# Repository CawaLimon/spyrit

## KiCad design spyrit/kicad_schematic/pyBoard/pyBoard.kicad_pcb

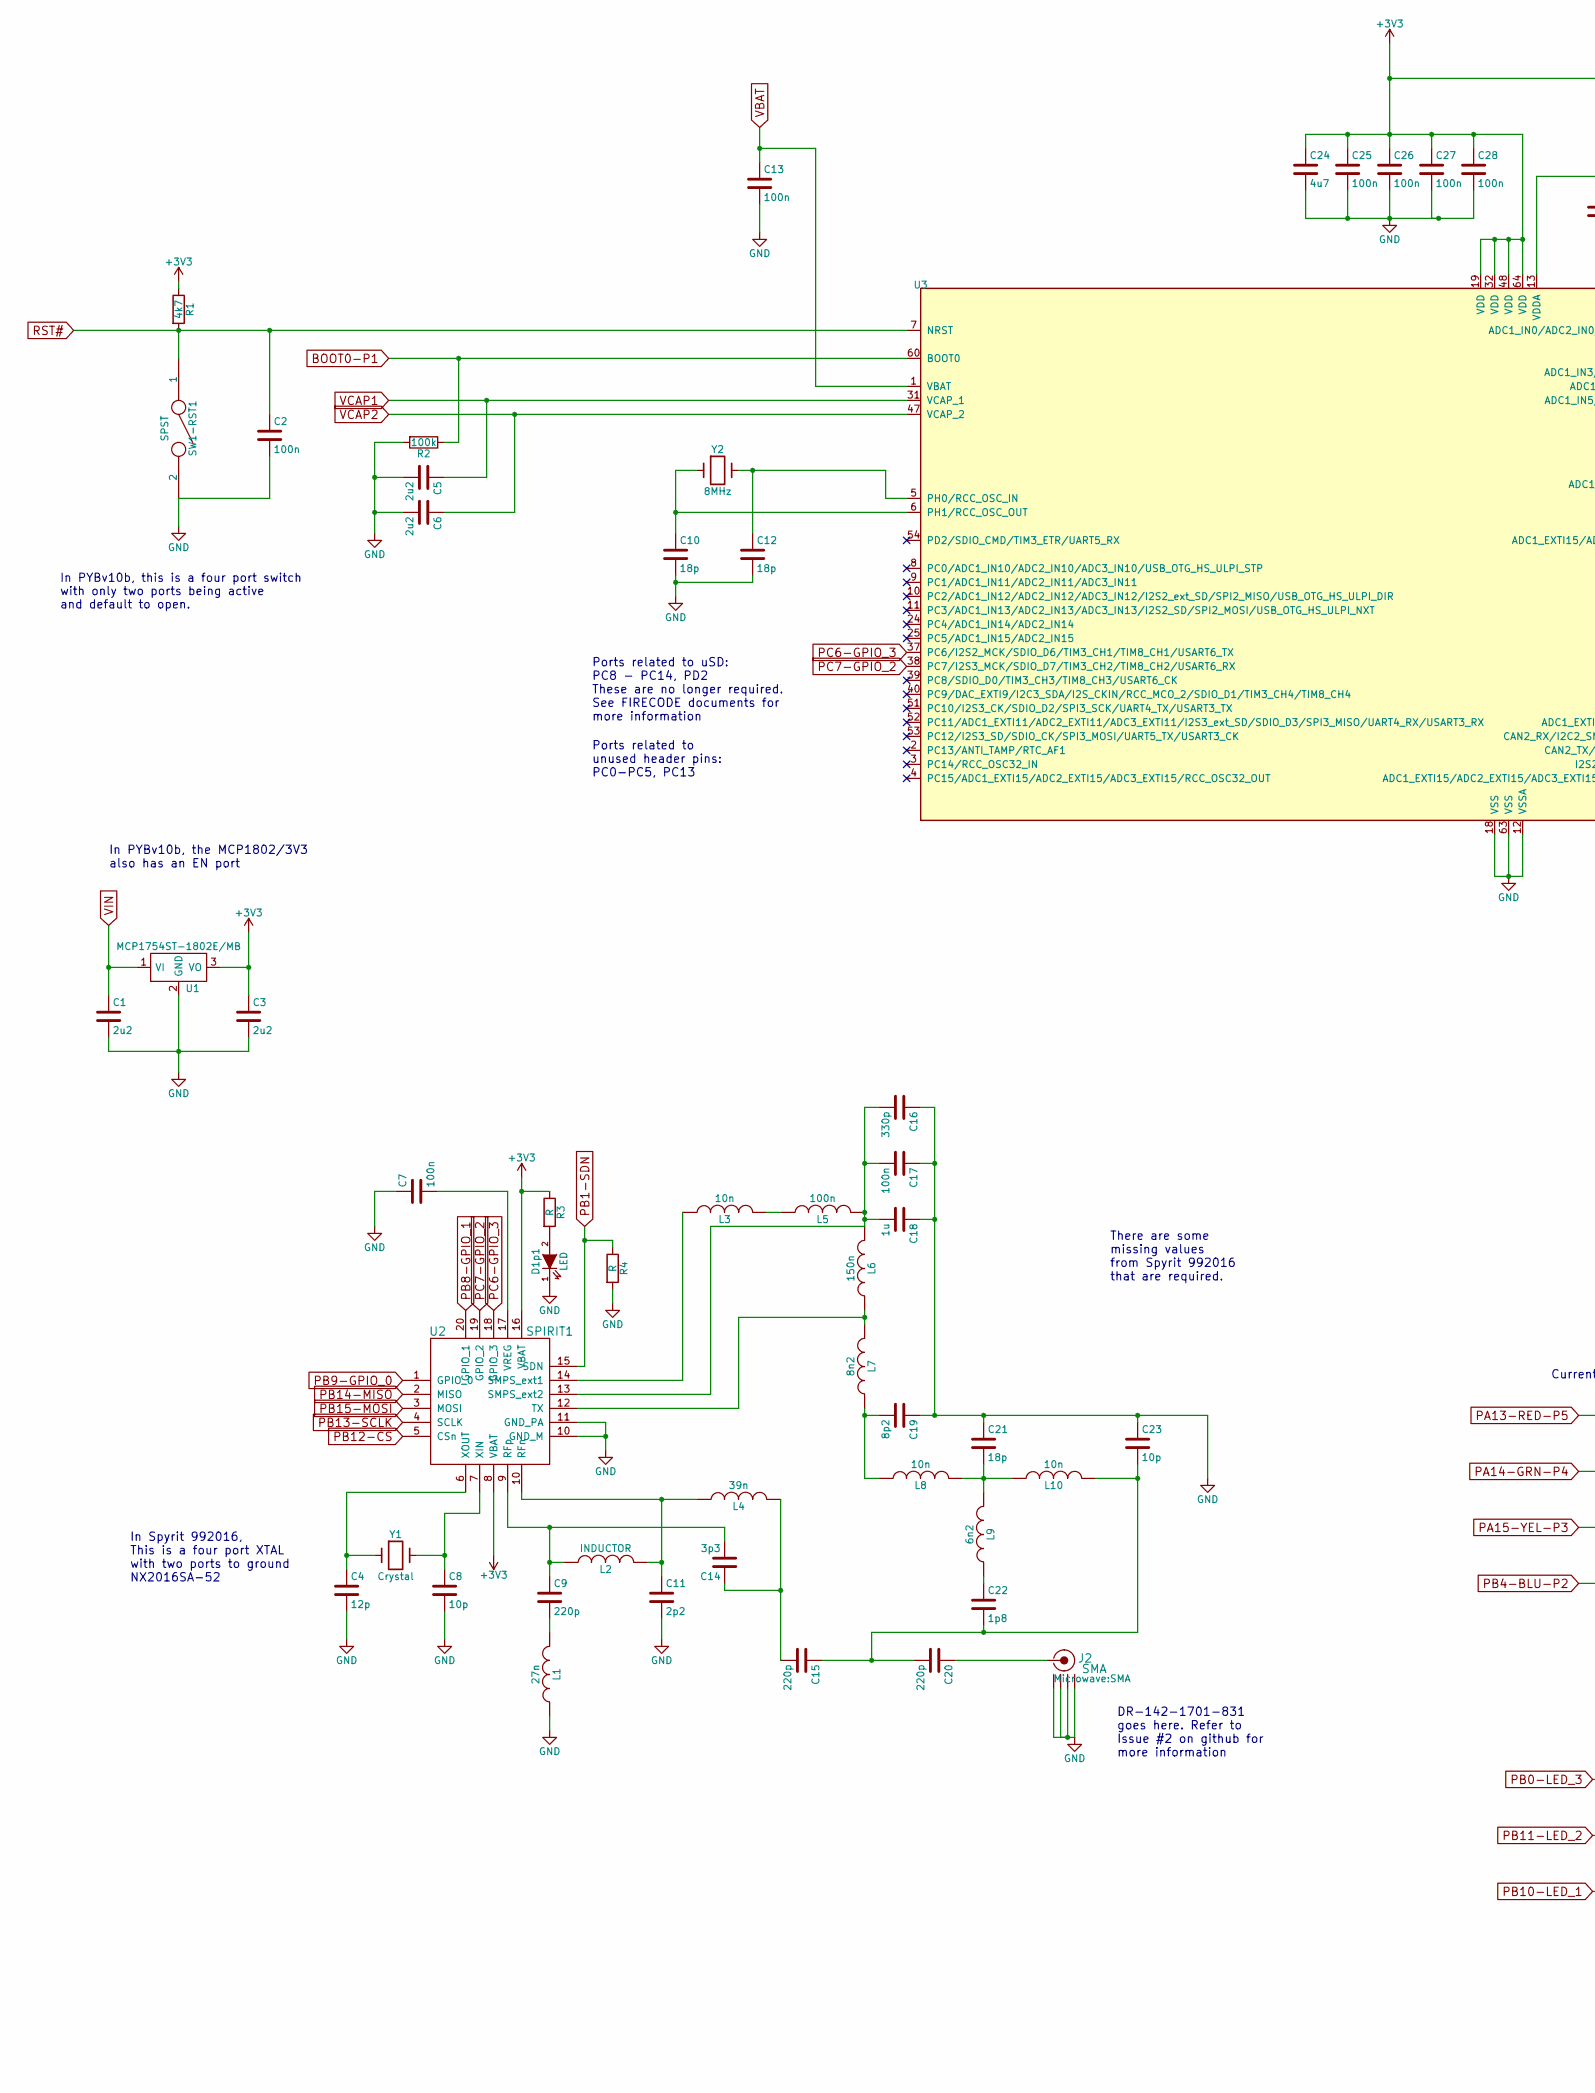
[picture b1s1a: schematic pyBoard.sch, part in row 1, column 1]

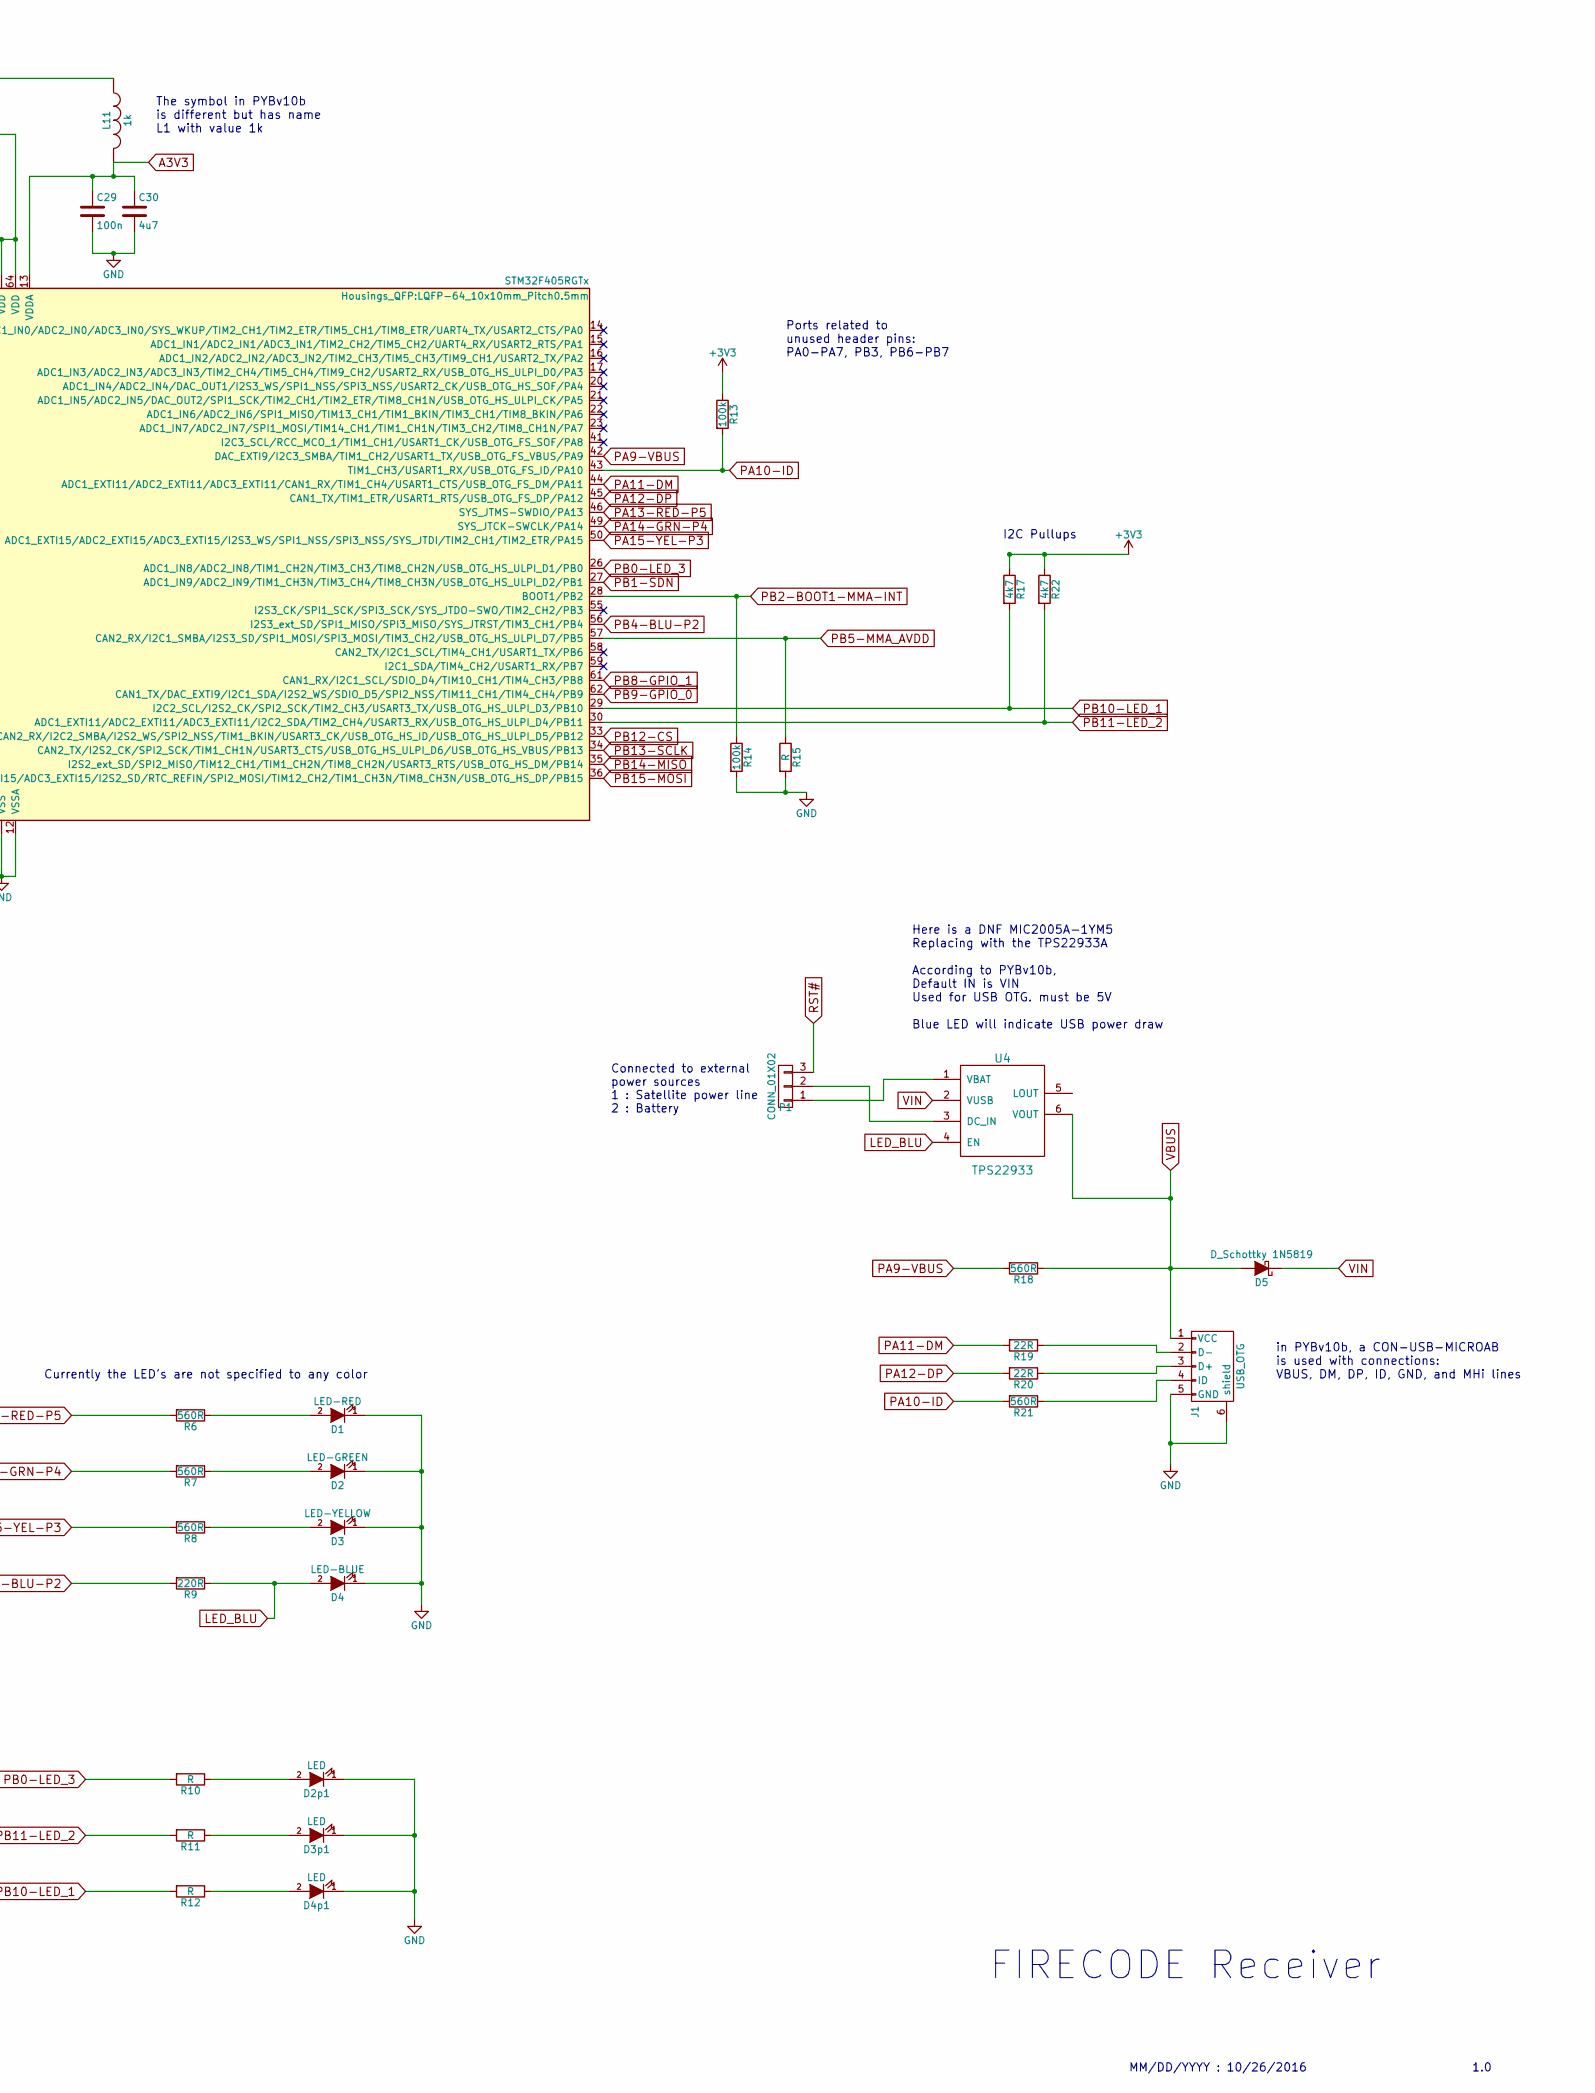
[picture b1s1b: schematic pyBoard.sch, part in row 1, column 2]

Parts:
C1, C3, C5, C6: 2u2; C_0603_HandSoldering
C2, C7, C13, C17, C25, C26, C27, C28, C29: 100n; C_0603_HandSoldering
C4: 12p; C_0603_HandSoldering
C8, C23: 10p; C_0603_HandSoldering
C9, C15, C20: 220p; C_0603_HandSoldering
C10, C12, C21: 18p; C_0603_HandSoldering
C11: 2p2; C_0603_HandSoldering
C14: 3p3; C_0603_HandSoldering
C16: 330p; C_0603_HandSoldering
C18: 1u; C_0603_HandSoldering
C19: 8p2; C_0603_HandSoldering
C22: 1p8; C_0603_HandSoldering
C24, C30: 4u7; C_0603_HandSoldering
D1: LED-RED; LED_0603
D1p1, D2p1, D3p1, D4p1: LED; LED_0603
D2: LED-GREEN; LED_0603
D3: LED-YELLOW; LED_0603
D4: LED-BLUE; LED_0603
D5: D_Schottky 1N5819; SMB_Handsoldering
J1: USB_OTG; USB_Micro-B
J2: SMA
L1: 27n; Choke_SMD_1206_Handsoldering
L2: INDUCTOR; Choke_SMD_1206_Handsoldering
L3, L8, L10: 10n; Choke_SMD_1206_Handsoldering
L4: 39n; Choke_SMD_1206_Handsoldering
L5: 100n; Choke_SMD_1206_Handsoldering
L6: 150n; Choke_SMD_1206_Handsoldering
L7: 8n2; Choke_SMD_1206_Handsoldering
L9: 6n2; Choke_SMD_1206_Handsoldering
L11: 1k; Choke_SMD_1206_Handsoldering
P1: CONN_01X02; PINHEAD1-3
R1, R17, R22: 4k7; R_0603_HandSoldering
R2, R13, R14: 100k; R_0603_HandSoldering
R3, R4, R10, R11, R12, R15: R; R_0603_HandSoldering
R6, R7, R8, R18, R21: 560R; R_0603_HandSoldering
R9: 220R; R_0603_HandSoldering
R19, R20: 22R; R_0603_HandSoldering
SW1-RST1: SPST; SW_SPST_B3U-3000P-B
U1: MCP1754ST-1802E/MB; SOT89-3_Housing_Handsoldering
U2: SPIRIT1; QFN-20-1EP_4x4mm_Pitch0.5mm
U3: STM32F405RGTx; LQFP-64_10x10mm_Pitch0.5mm
U4: TPS22933; UQFN_1.5mm_x_1.5mm
Y1: Crystal; Crystal_SMD_5032_2Pads
Y2: 8MHz; Crystal_SMD_5032_2Pads

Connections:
+3V3: C3.1, C24.1, C25.1, C26.1, C27.1, C28.1, L11.1, R1.1, R3.1, R13.1, R17.1, R22.1, U1.3 (VO), U2.8 (VBAT), U2.16 (VBAT), U3.19 (VDD), U3.32 (VDD), U3.48 (VDD), U3.64 (VDD)
A3V3: C29.1, C30.1, L11.2, U3.13 (VDDA)
BOOT0-P1: R2.1, U3.60 (BOOT0)
LED_BLU: D4.2 (A), R9.1, U4.4 (EN)
unnamed: C4.1, U2.6 (XOUT), Y1.1
unnamed: C7.2, U2.17 (VREG)
unnamed: C8.1, U2.7 (XIN), Y1.2
unnamed: C9.2, L1.2
unnamed: C10.1, U3.6 (PH1/RCC_OSC_OUT), Y2.1
unnamed: C12.1, U3.5 (PH0/RCC_OSC_IN), Y2.2
unnamed: C14.1, C15.2, L4.2
unnamed: C9.1, C14.2, L2.1, U2.9 (RFp)
unnamed: C15.1, C20.2, C22.2, C23.2, L10.2
unnamed: C16.2, C17.2, C18.2, L5.2, L6.2, U2.13 (SMPS_ext2)
unnamed: C19.2, L7.1, L8.1
unnamed: C20.1, J2.1 (RF)
unnamed: C21.2, L8.2, L9.2, L10.1
unnamed: C22.1, L9.1
unnamed: D1.2 (A), R6.1
unnamed: D1p1.2 (A), R3.2
unnamed: D2.2 (A), R7.1
unnamed: D2p1.2 (A), R10.1
unnamed: D3.2 (A), R8.1
unnamed: D3p1.2 (A), R11.1
unnamed: D4p1.2 (A), R12.1
unnamed: J1.2 (D-), R19.1
unnamed: J1.3 (D+), R20.1
unnamed: J1.4 (ID), R21.1
unnamed: L3.1, U2.14 (SMPS_ext1)
unnamed: L3.2, L5.1
unnamed: L6.1, L7.2, U2.12 (TX)
unnamed: P1.1, U4.1 (VBAT)
unnamed: P1.2, U4.3 (DC_IN)
PA9-VBUS: R18.2, U3.42 (DAC_EXTI9/I2C3_SMBA/TIM1_CH2/USART1_TX/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)
PA10-ID: R13.2, R21.2, U3.43 (TIM1_CH3/USART1_RX/USB_OTG_FS_ID/PA10)
PA11-DM: R19.2, U3.44 (ADC1_EXTI11/ADC2_EXTI11/ADC3_EXTI11/CAN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)
PA12-DP: R20.2, U3.45 (CAN1_TX/TIM1_ETR/USART1_RTS/USB_OTG_FS_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)
PA13-RED-P5: R6.2, U3.46 (SYS_JTMS-SWDIO/PA13)
PA14-GRN-P4: R7.2, U3.49 (SYS_JTCK-SWCLK/PA14)
PA15-YEL-P3: R8.2, U3.50 (ADC1_EXTI15/ADC2_EXTI15/ADC3_EXTI15/I2S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)
PB0-LED_3: R10.2, U3.26 (ADC1_IN8/ADC2_IN8/TIM1_CH2N/TIM3_CH3/TI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)
PB1-SDN: R4.1, U2.15 (SDN), U3.27 (ADC1_IN9/ADC2_IN9/TIM1_CH3N/TIM3_CH4/TI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)
PB2-BOOT1-MMA-INT: R14.1, U3.28 (BOOT1/PB2)
PB4-BLU-P2: R9.2, U3.56 (I2S3_ext_SD/SPI1_MISO/SPI3_MISO/SYS_JTR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)
PB5-MMA_AVDD: R15.1, U3.57 (CAN2_RX/I2C1_SMBA/I2S3_SD/SPI1_MOSI/SPI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)
PB8-GPIO_1: U2.20 (GPIO_1), U3.61 (CAN1_RX/I2C1_SCL/SDIO_D4/TIM10_CH1/TIM4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)
PB9-GPIO_0: U2.1 (GPIO_0), U3.62 (CAN1_TX/DAC_EXTI9/I2C1_SDA/I2S2_WS/SDIO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)
PB10-LED_1: R12.2, R17.2, U3.29 (I2C2_SCL/I2S2_CK/SPI2_SCK/TIM2_CH3/USAR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)
PB11-LED_2: R11.2, R22.2, U3.30 (ADC1_EXTI11/ADC2_EXTI11/ADC3_EXTI11/I2C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)
PB12-CS: U2.5 (CSn), U3.33 (CAN2_RX/I2C2_SMBA/I2S2_WS/SPI2_NSS/TIM1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)
PB13-SCLK: U2.4 (SCLK), U3.34 (CAN2_TX/I2S2_CK/SPI2_SCK/TIM1_CH1N/USAR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)
PB14-MISO: U2.2 (MISO), U3.35 (I2S2_ext_SD/SPI2_MISO/TIM12_CH1/TIM1_CH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)
PB15-MOSI: U2.3 (MOSI), U3.36 (ADC1_EXTI15/ADC2_EXTI15/ADC3_EXTI15/I2S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)
PC6-GPIO_3: U2.18 (GPIO_3), U3.37 (PC6/I2S2_MCK/SDIO_D6/TIM3_CH1/TIM8_CH1/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)
PC7-GPIO_2: U2.19 (GPIO_2), U3.38 (PC7/I2S3_MCK/SDIO_D7/TIM3_CH2/TIM8_CH2/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)
RST#: C2.1, P1.3, R1.2, SW1-RST1.1, U3.7 (NRST)
VBAT: C13.1, U3.1 (VBAT)
VBUS: D5.2 (A), J1.1 (VCC), R18.1, U4.6 (VOUT)
VCAP1: C5.1, U3.31 (VCAP_1)
VCAP2: C6.1, U3.47 (VCAP_2)
VIN: C1.1, D5.1 (K), U1.1 (VI), U4.2 (VUSB)

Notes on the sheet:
In PYBv10b, this is a four port switch with only two ports being active and default to open.
Ports related to uSD: PC8 - PC14, PD2 These are no longer required. See FIRECODE documents for more information
The symbol in PYBv10b is different but has name L1 with value 1k
In PYBv10b, the MCP1802/3V3 also has an EN port
Currently the LED's are not specified to any color
in PYBv10b, a CON-USB-MICROAB is used with connections: VBUS, DM, DP, ID, GND, and MHi lines
Here is a DNF MIC2005A-1YM5 Replacing with the TPS22933A According to PYBv10b, Default IN is VIN Used for USB OTG. must be 5V Blue LED will indicate USB power draw
I2C Pullups
Ports related to unused header pins: PC0-PC5, PC13
Ports related to unused header pins: PA0-PA7, PB3, PB6-PB7
In Spyrit 992016, This is a four port XTAL with two ports to ground NX2016SA-52
DR-142-1701-831 goes here. Refer to Issue #2 on github for more information
There are some missing values from Spyrit 992016 that are required.
FIRECODE Receiver
MM/DD/YYYY : 10/26/2016
1.0
Connected to external power sources 1 : Satellite power line 2 : Battery

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
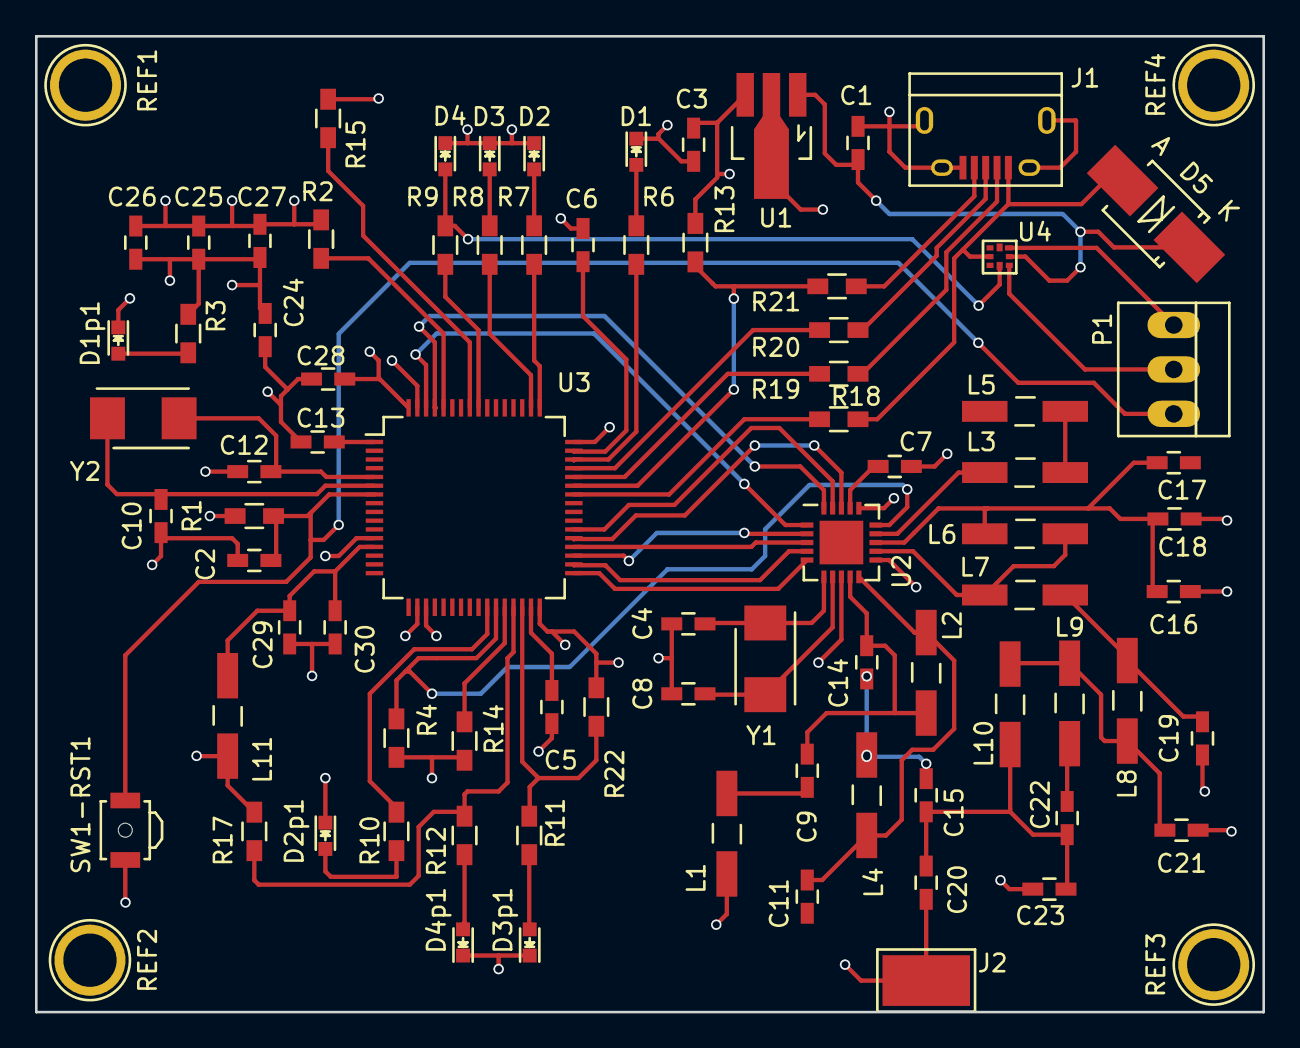
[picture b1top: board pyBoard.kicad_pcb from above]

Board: 4 copper layers, 70.2 x 55.8 mm, 84 parts (0 on the bottom side), 63 nets.

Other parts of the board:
REF1, REF2, REF3, REF4: 1pin

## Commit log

2016-09-09 added
2016-09-09 added spirit1 drivers (inc)
2016-09-12 Add Spyrit electrical schematic
2016-10-26 [Derek] intial commit of the pyboard schematics
2016-10-26 [Derek] finished pyboard schematic missing only two components, the MIC2005A-1YM5 and the headers
2016-10-27 [Derek] combining the pyboard and the spyrit onto one schematic
2016-10-27 [Derek] adding FIRECODEv1.0 schematic as a pdf
2016-11-03 [Derek] assigning footprints to components, required many elements from github/kicad/
2016-11-08 [Derek] created custom package UQFP and subsequently finished the netlist
2016-11-09 [Derek] inital commit for PCB layout, FIRECODE schematic v2.0 up
2016-11-09 [Derek] wiring intial commit
2016-11-09 [Derek] updating to FIRECODE schematic v3
2016-11-09 Added AES, LDCR, and most other things
2016-11-09 added stuff
2016-11-12 [Derek] implementing 5/9 of pcb review improvements
2016-11-21 Adding DP1 Project Report intial commit
2016-11-21 [Derek] creating multiple layered PCB board with (hopefully) valid 3V3 and GND layers and connections
2016-11-22 Added Mounting holes
2016-11-22 Updated 3D diagram
2016-11-22 adding pcb layout
2017-02-06 [Derek] updating whitepaper with .pdf version
2017-02-06 [Derek] removing latex residuals
2017-09-07 added micropython build
2017-09-07 removed unnecessary upy files
